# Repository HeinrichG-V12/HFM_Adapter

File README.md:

# HFM Adapter

## With this adapter it is possible to replace any HLM with any HFM

## Development status

- Hardware: Revision 1.0 done
  - [**Revision 1.0 is erroneous, swapped pins on TLE42764 and TLE4252D.**](./hardware/Rev1.0/README.md)
  - [Revision 1.1 done](./hardware/Rev1.1/README.md)
- Software: Version 1.0 done

### HFM Adapter based on

- STM32 G431KB Nucleo-32 Board
- ST M24M02 2MBit serial I²C EEPROM to store the tables and configuration
- TI REF02 +5.0v precision voltage reference, +-0.2%
- Infineon TLE4252D tracking regulator 250mA
- TI OPA2992 output operation amplifier

### Nucleo-32 modifications

A few changes need to be made to the Nucleo-32 board before it can be used:

- SB1 and SB12 removed (disconnect PA2 and PA3 from T_VCP_TX and T_VCP_RX of ST-Link)
- SB14 installed (connect PA3 to CN3 Pin 10)
- SB9 and SB10 installed (connect external 24MHz HSE CLK)

### Features

- Automotive grade components
- 4 layer PCB
- Configuration via TunerStudio

### Inputs

- two HFM buffered analog inputs (0v - 5v) with overvoltage protection 
- USB for configuration
- VBat input for voltage monitoring 

### Outputs

- two analog outputs
- two precision reference 5.0v outputs for HFM
- two Vbat outputs for HFM

### Housing

- Header: Amphenol ATM13-12PA
- Enclosure: Amphenol AIPXE-325X4

### Pin terminal for BMW M70 adapter

- pin terminal 1252 1718125
- connector boot 1252 1711262
- pins
  - 0.5 - 1.0mm² 6113 1376191
  - 1.0mm² - 2.5mm² 6113 1376193
  - 2.5mm² - 4.0mm² 6113 1376195

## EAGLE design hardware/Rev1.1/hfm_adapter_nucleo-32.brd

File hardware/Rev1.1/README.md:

# HFM Adapter

## Revision 1.1

[Schematic](./hfm_adapter_nucleo-32.pdf)

Pinout

|Pin#|Wire size|Main color|Second color|Signal|
|----|---------|----------|------------|------|
|1|0.5mm²|brown|-|signal ground|
|2|0.5mm²|brown|-|signal ground|
|3|0.5mm²|red|blue|VBat|
|4|0.5mm²|red|blue|VBat|
|5|0.5mm²|violett|black|5v reference voltage for HFM|
|6|0.5mm²|brown|-|signal ground|
|7|0.5mm²|red|blue|VBat|
|8|0.5mm²|violet|black|5v reference voltage for HFM|
|9|0.5mm²|violet|yellow|Channel 1 input from HFM|
|10|0.5mm²|orange|yellow|Channel 2 input from HFM|
|11|0.5mm²|violet|green|Channel 1 output to ECM|
|12|0.5mm²|orange|green|Channel 2 output to ECM|

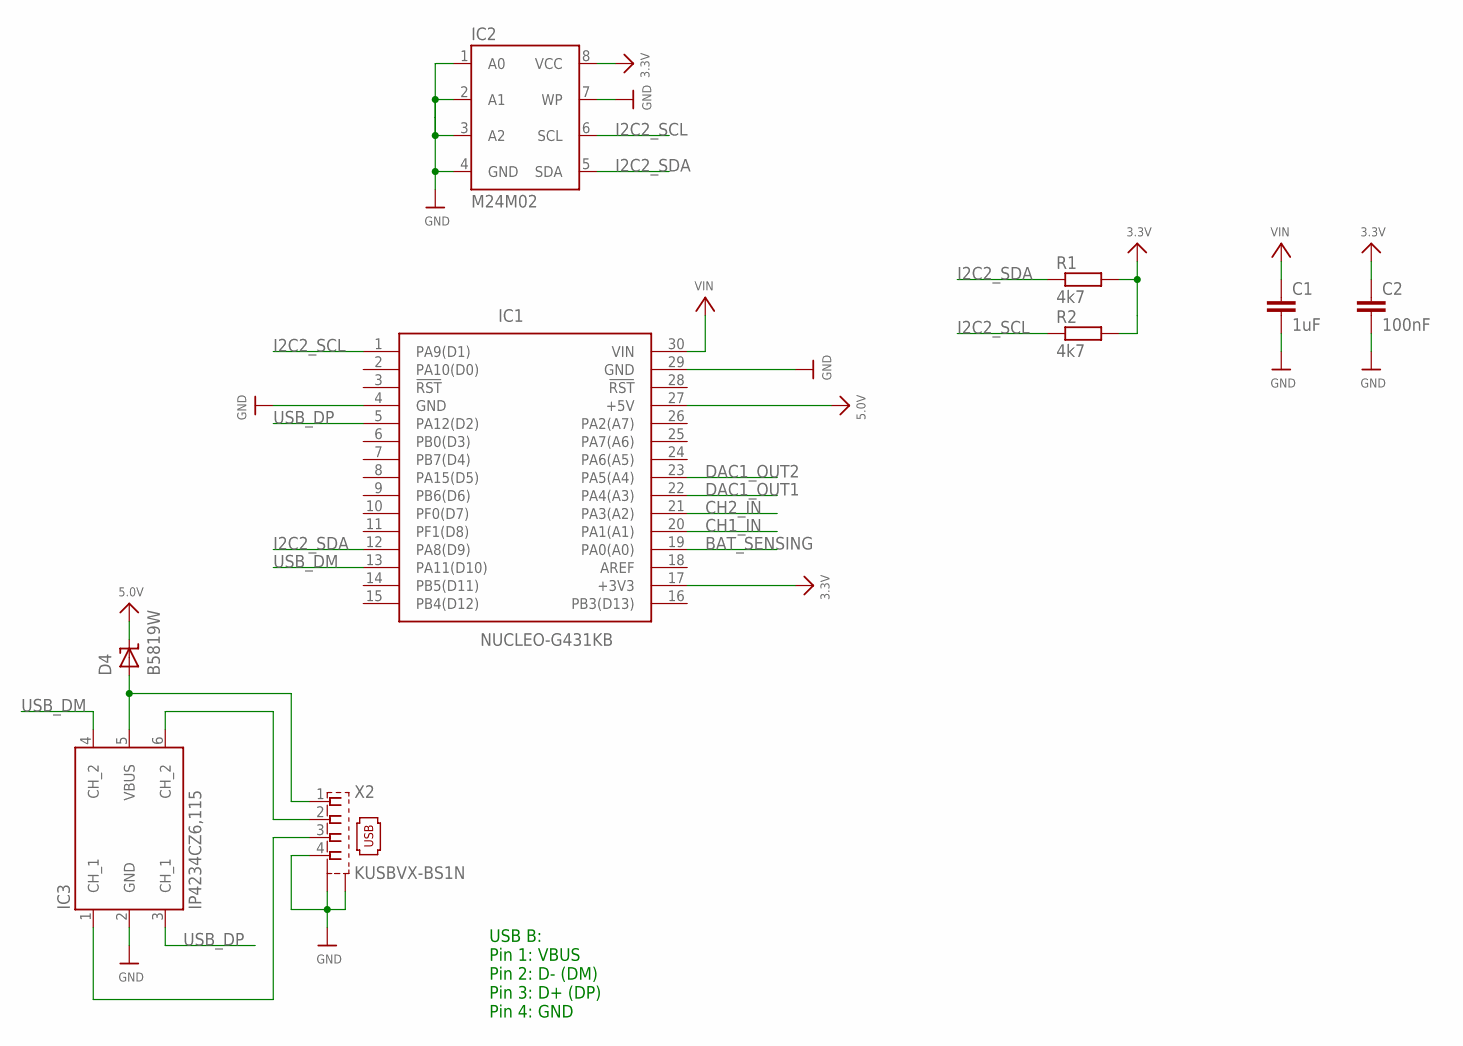
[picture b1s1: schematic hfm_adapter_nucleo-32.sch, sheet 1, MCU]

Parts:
C1: 1uF; C0805
C2: 100nF; C0805
D4: B5819W; SOD-123
IC1: NUCLEO-G431KB; DIPS1524W66P254L5029H1500Q30N
IC2: M24M02; SO8
IC3: IP4234CZ6,115; SOT95P275X110-6N
R1, R2: 4k7; R0805
X2: KUSBVX-BS1N

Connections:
3.3V: C2.1, IC1.17 (+3V3), IC2.8 (VCC), R1.2, R2.2; also elsewhere on the board
5.0V: D4.C, IC1.27 (+5V); also elsewhere on the board
BAT_SENSING: IC1.19 (PA0(A0)); also elsewhere on the board
CH1_IN: IC1.20 (PA1(A1)); also elsewhere on the board
CH2_IN: IC1.21 (PA3(A2)); also elsewhere on the board
DAC1_OUT1: IC1.22 (PA4(A3)); also elsewhere on the board
DAC1_OUT2: IC1.23 (PA5(A4)); also elsewhere on the board
GND: C1.2, C2.2, IC1.4 (GND), IC1.29 (GND), IC2.1 (A0), IC2.2 (A1), IC2.3 (A2), IC2.4 (GND), IC2.7 (WP), IC3.2 (GND), X2.4, X2.M1 (S1), X2.M2 (S2); also elsewhere on the board
I2C2_SCL: IC1.1 (PA9(D1)), IC2.6 (SCL), R2.1; also elsewhere on the board
I2C2_SDA: IC1.12 (PA8(D9)), IC2.5 (SDA), R1.1; also elsewhere on the board
unnamed: IC3.1 (CH_1), X2.3
unnamed: IC3.6 (CH_2), X2.2
unnamed: D4.A, IC3.5 (VBUS), X2.1
USB_DM: IC1.13 (PA11(D10)), IC3.4 (CH_2)
USB_DP: IC1.5 (PA12(D2)), IC3.3 (CH_1)
VIN: C1.1, IC1.30 (VIN); also elsewhere on the board

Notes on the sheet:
USB B: Pin 1: VBUS Pin 2: D- (DM) Pin 3: D+ (DP) Pin 4: GND

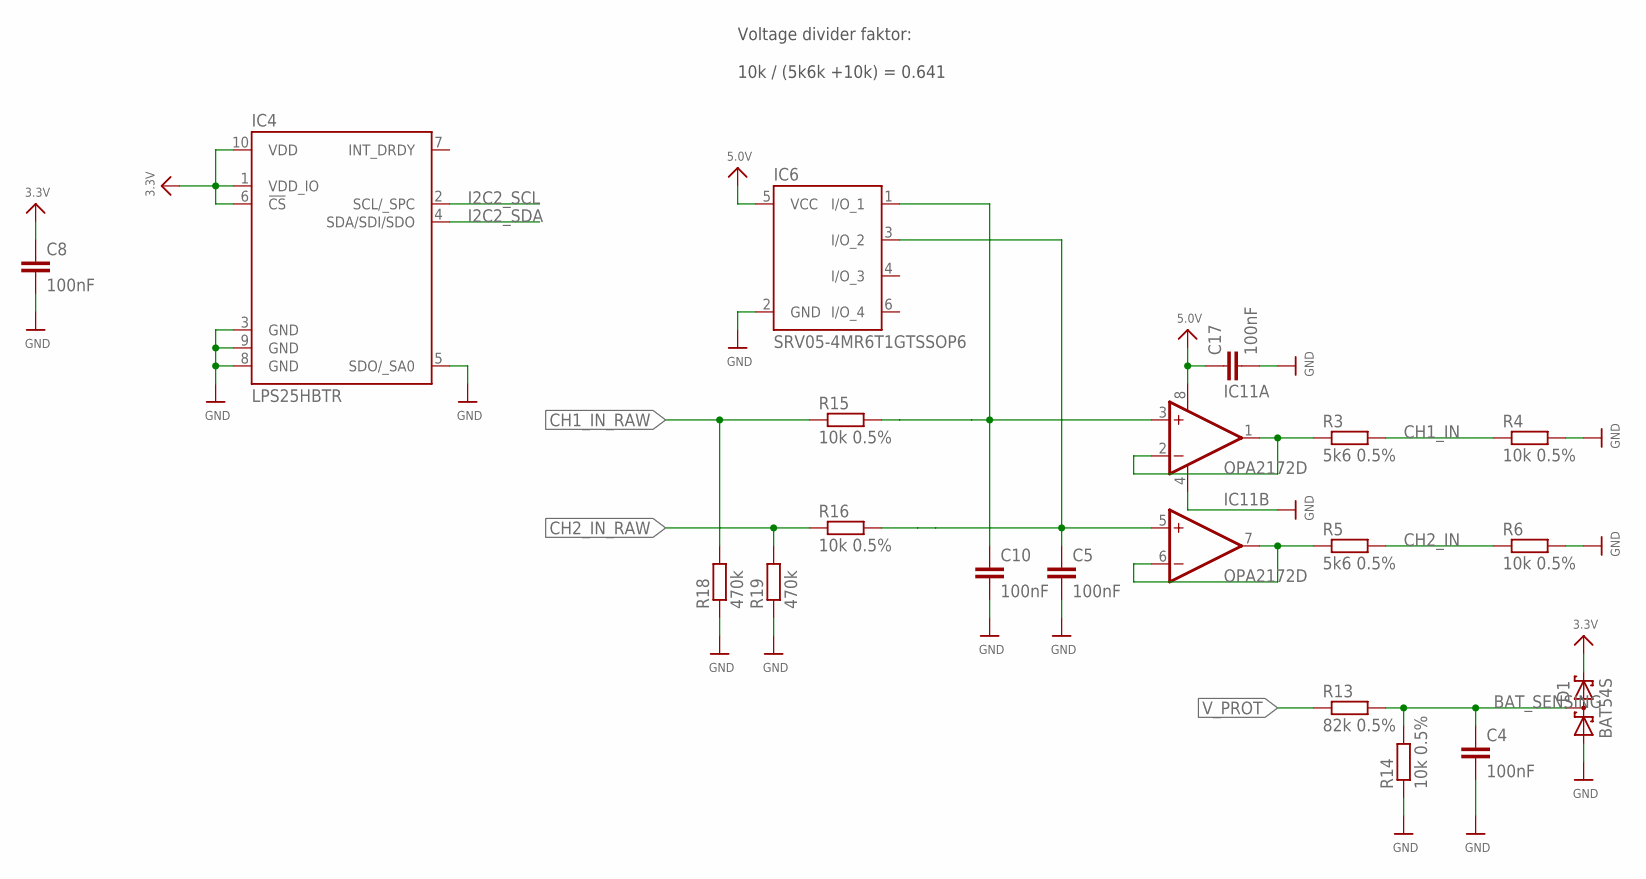
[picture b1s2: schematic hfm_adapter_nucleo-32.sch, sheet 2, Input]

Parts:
C4, C5, C8, C10, C17: 100nF; C0805
D1: BAT54S; SOT23
IC4: LPS25HBTR
IC6: SRV05-4MR6T1GTSSOP6; TSSOP6
IC11: OPA2172D; SO08
R3, R5: 5k6 0.5%; R0805
R4, R6, R14, R15, R16: 10k 0.5%; R0805
R13: 82k 0.5%; R0805
R18, R19: 470k; R0805

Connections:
3.3V: C8.1, D1.2 (K2), IC4.1 (VDD_IO), IC4.6 (!CS), IC4.10 (VDD); also elsewhere on the board
5.0V: C17.1, IC6.5 (VCC), IC11.8 (V+); also elsewhere on the board
BAT_SENSING: C4.1, D1.3 (K1A2), R13.2, R14.2; also elsewhere on the board
CH1_IN: R3.2, R4.1; also elsewhere on the board
CH1_IN_RAW: R15.1, R18.2; also elsewhere on the board
CH2_IN: R5.2, R6.1; also elsewhere on the board
CH2_IN_RAW: R16.1, R19.2; also elsewhere on the board
GND: C4.2, C5.2, C8.2, C10.2, C17.2, D1.1 (A1), IC4.3 (GND), IC4.5 (SDO/_SA0), IC4.8 (GND), IC4.9 (GND), IC6.2 (GND), IC11.4 (V-), R4.2, R6.2, R14.1, R18.1, R19.1; also elsewhere on the board
I2C2_SCL: IC4.2 (SCL/_SPC); also elsewhere on the board
I2C2_SDA: IC4.4 (SDA/SDI/SDO); also elsewhere on the board
unnamed: IC11.1 (OUT), IC11.2 (-IN), R3.1
unnamed: C10.1, IC6.1 (I/O_1), IC11.3 (+IN), R15.2
unnamed: IC11.6 (-IN), IC11.7 (OUT), R5.1
unnamed: C5.1, IC6.3 (I/O_2), IC11.5 (+IN), R16.2
V_PROT: R13.1; also elsewhere on the board

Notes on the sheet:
Voltage divider faktor: 10k / (5k6k +10k) = 0.641

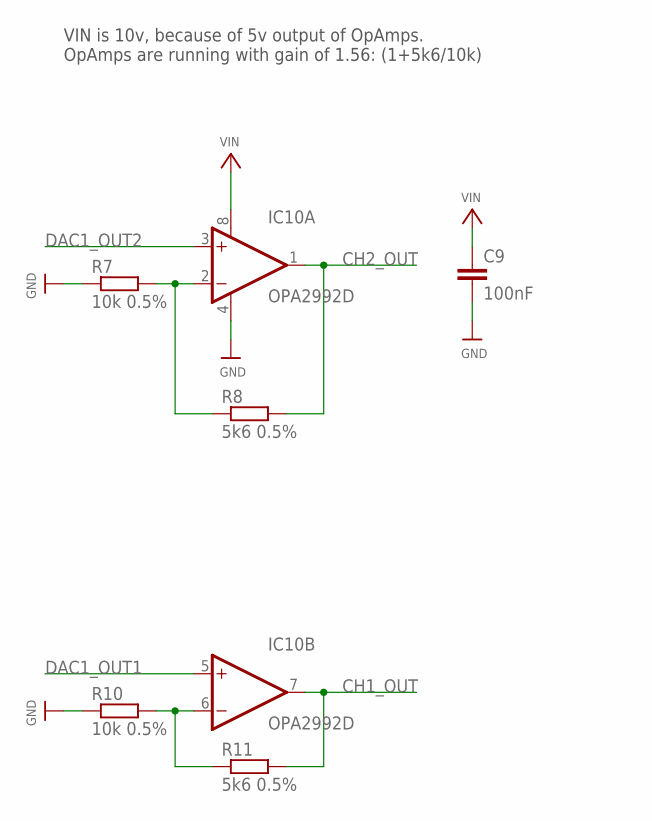
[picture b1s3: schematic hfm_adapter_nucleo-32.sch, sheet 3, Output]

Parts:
C9: 100nF; C0805
IC10: OPA2992D; SO08
R7, R10: 10k 0.5%; R0805
R8, R11: 5k6 0.5%; R0805

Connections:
CH1_OUT: IC10.7 (OUT), R11.2; also elsewhere on the board
CH2_OUT: IC10.1 (OUT), R8.2; also elsewhere on the board
DAC1_OUT1: IC10.5 (+IN); also elsewhere on the board
DAC1_OUT2: IC10.3 (+IN); also elsewhere on the board
GND: C9.2, IC10.4 (V-), R7.1, R10.1; also elsewhere on the board
unnamed: IC10.6 (-IN), R10.2, R11.1
unnamed: IC10.2 (-IN), R7.2, R8.1
VIN: C9.1, IC10.8 (V+); also elsewhere on the board

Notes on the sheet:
VIN is 10v, because of 5v output of OpAmps. OpAmps are running with gain of 1.56: (1+5k6/10k)

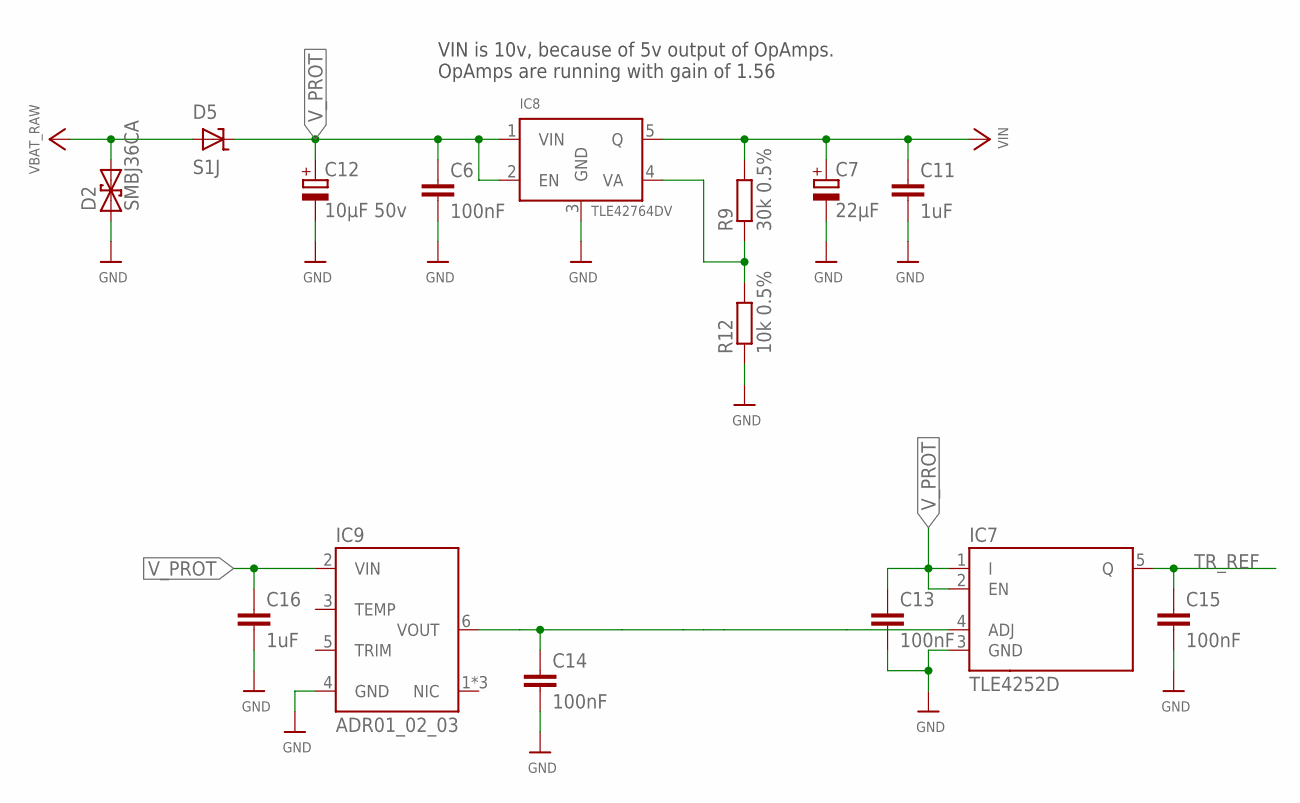
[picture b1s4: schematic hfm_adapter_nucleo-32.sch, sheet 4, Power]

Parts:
C6: 100nF; C1206
C7: 22µF; PANASONIC_C
C11, C16: 1uF; C0805
C12: 10µF 50v; PANASONIC_D
C13, C14, C15: 100nF; C0805
D2: SMBJ36CA; DO214AA
D5: S1J; DO214AC
IC7: TLE4252D; TO-252-5-INF
IC8: TLE42764DV; TO-252-5-INF
IC9: ADR01_02_03; SOIC8
R9: 30k 0.5%; R0805
R12: 10k 0.5%; R0805

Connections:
GND: C6.2, C7.-, C11.2, C12.-, C13.2, C14.2, C15.2, C16.2, D2.A (1), IC7.3 (GND), IC8.3 (GND), IC9.4 (GND), R12.1; also elsewhere on the board
unnamed: IC8.4 (VA), R9.1, R12.2
TR_REF: C15.1, IC7.5 (Q); also elsewhere on the board
VBAT_RAW: D2.C (2), D5.A; also elsewhere on the board
VIN: C7.+, C11.1, IC8.5 (Q), R9.2; also elsewhere on the board
VREF: C14.1, IC7.4 (ADJ), IC9.6 (VOUT)
V_PROT: C6.1, C12.+, C13.1, C16.1, D5.C, IC7.1 (I), IC7.2 (EN), IC8.1 (VIN), IC8.2 (EN), IC9.2 (VIN); also elsewhere on the board

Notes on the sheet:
VIN is 10v, because of 5v output of OpAmps. OpAmps are running with gain of 1.56

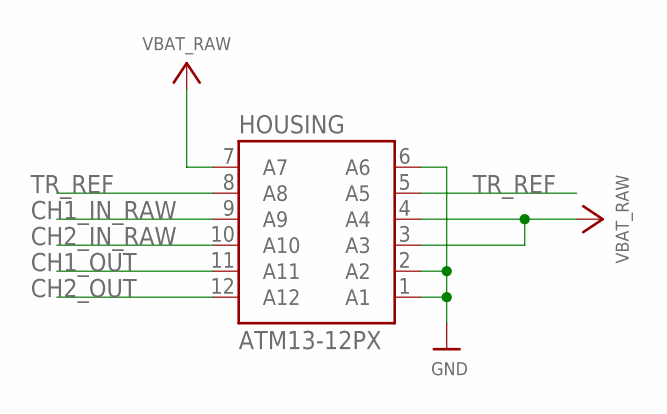
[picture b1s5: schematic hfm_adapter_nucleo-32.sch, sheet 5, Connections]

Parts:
HOUSING: ATM13-12PX

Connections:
CH1_IN_RAW: HOUSING.9 (A9); also elsewhere on the board
CH1_OUT: HOUSING.11 (A11); also elsewhere on the board
CH2_IN_RAW: HOUSING.10 (A10); also elsewhere on the board
CH2_OUT: HOUSING.12 (A12); also elsewhere on the board
GND: HOUSING.1 (A1), HOUSING.2 (A2), HOUSING.6 (A6); also elsewhere on the board
TR_REF: HOUSING.5 (A5), HOUSING.8 (A8); also elsewhere on the board
VBAT_RAW: HOUSING.3 (A3), HOUSING.4 (A4), HOUSING.7 (A7); also elsewhere on the board

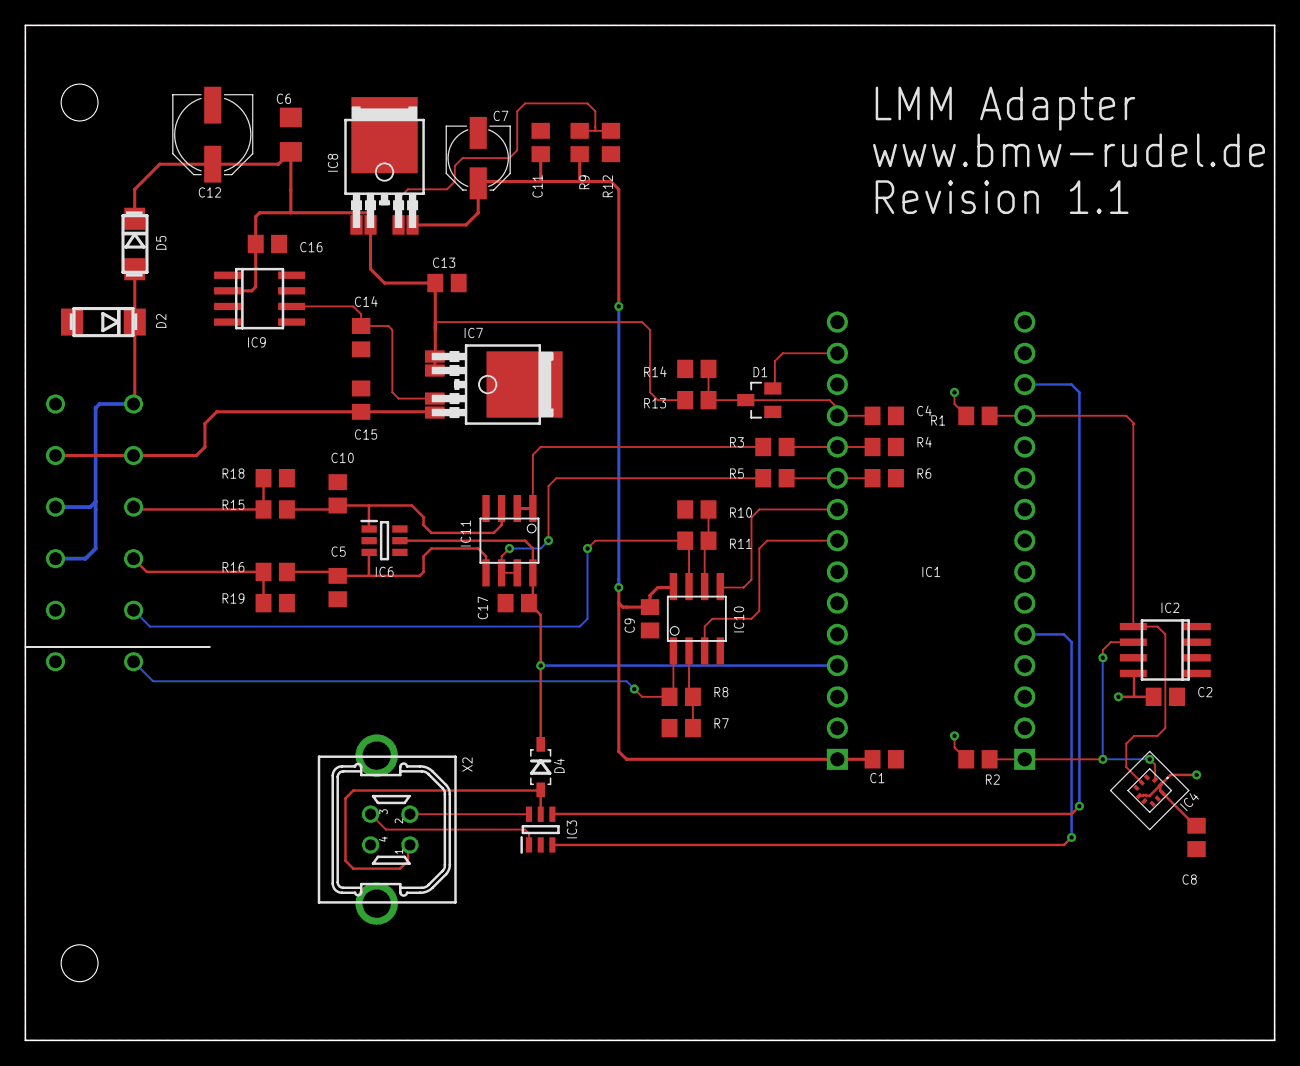
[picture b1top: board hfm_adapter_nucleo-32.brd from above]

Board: 4 copper layers, 101.6 x 82.5 mm, 50 parts (0 on the bottom side), 31 nets.

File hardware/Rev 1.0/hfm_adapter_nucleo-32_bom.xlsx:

Qty | Value | Device | Package | Parts | Description
10 | 100nF | C-EUC0805 | C0805 | C2, C4, C5, C8, C9, C10, C13, C14, C15, C17 | CAPACITOR, European symbol
1 | 100nF | C-EUC1206 | C1206 | C6 | CAPACITOR, European symbol
3 | 10k | R-EU_R0805 | R0805 | R14, R15, R16 | RESISTOR, European symbol
1 | 10k 0.5% | R-EU_R0805 | R0805 | R12 | RESISTOR, European symbol
1 | 10ÂµF 50v | CPOL-EUD | PANASONIC_D | C12 | POLARIZED CAPACITOR, European symbol
4 | 17k 0.5% | R-EU_R0805 | R0805 | R3, R5, R7, R10 | RESISTOR, European symbol
3 | 1uF | C-EUC0805 | C0805 | C1, C11, C16 | CAPACITOR, European symbol
1 | 22µF | CPOL-EUC | PANASONIC_C | C7 | POLARIZED CAPACITOR, European symbol
1 | 30k 0.5% | R-EU_R0805 | R0805 | R9 | RESISTOR, European symbol
4 | 33k 0.5% | R-EU_R0805 | R0805 | R4, R6, R8, R11 | RESISTOR, European symbol
2 | 470k | R-EU_R0805 | R0805 | R18, R19 | RESISTOR, European symbol
2 | 4k7 | R-EU_R0805 | R0805 | R1, R2 | RESISTOR, European symbol
1 | 82k | R-EU_R0805 | R0805 | R13 | RESISTOR, European symbol
1 | ATM13-12PX | ATM13-12PX | ATM13-12PX | HOUSING
1 | B5819W | SHOTTKYSOD-123 | SOD-123 | D4
1 | BAT54S | BAT54S | SOT23 | D1 | Schottky barrier (double) diodesPlanar Schottky barrier diodes encapsulated in 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
1 | IP4234CZ6,115 | IP4234CZ6,115 | SOT95P275X110-6N | IC3 | ESD Suppressors / TVS Diodes ESD PRTCT/HI SPD INF ZEN LOW VLTG CLMP
1 | KUSBVX-BS1N | KUSBVX-BS1N | KUSBVX-BS1N | X2 | USB B-type Receptacle Vertical, 4 Position, Through Hole
1 | LPS25HBTR | LPS25HBTR | LPS25HBTR | IC4 | Board Mount Pressure Sensor 26kPa to 126kPa Absolute 10-Pin HLGA T/R
1 | M24M02 | EEPROM_I2CSO8 | SO8 | IC2 | IÂ²C EEPROM IC, i.e. FT24C256A
1 | NUCLEO-G431KB | NUCLEO-G431KB | DIPS1524W66P254L5029H1500Q30N | IC1 | STM32 Nucleo-32 development board
1 | OPA2172D | OPA2172D | SO08 | IC11 | Operational Amplifier
1 | OPA2992D | OPA2172D | SO08 | IC10 | Operational Amplifier
1 | REF02D | REF02D | SO08 | IC5 | VOLTAGE REFERENCE
1 | S1J | SHOTTKYSMA | DO214AC | D5
1 | SMBJ36CA | TVS_BIA | DO214AA | D2
1 | SRV05-4MR6T1GTSSOP6 | SRV05-4MR6T1GTSSOP6 | TSSOP6 | IC6
1 | TLE4252D | TLE4252D | TO252-51 | IC9 | Infineon Tracking regualtor
1 | TLE42764_ADJDV | TLE42764_ADJDV | TO252-51 | IC8

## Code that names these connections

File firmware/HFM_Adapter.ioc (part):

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Mcu.Name=STM32G431K(6-8-B)Tx
Mcu.Package=LQFP32
Mcu.UserName=STM32G431KBTx
PA0.Mode=IN1-Single-Ended
PA0.Signal=ADC1_IN1
PA1.Mode=IN2-Single-Ended
PA1.Signal=ADC1_IN2
PA11.Mode=Device
PA11.Signal=USB_DM
PA12.Mode=Device
PA12.Signal=USB_DP
PA13.GPIOParameters=GPIO_Label
PA13.GPIO_Label=T_SWDIO
PA13.Mode=Serial_Wire
PA13.Signal=SYS_JTMS-SWDIO
PA14.GPIOParameters=GPIO_Label
PA14.GPIO_Label=T_SWCLK
PA14.Mode=Serial_Wire
PA14.Signal=SYS_JTCK-SWCLK
PA2.Mode=IN3-Single-Ended
PA2.Signal=ADC1_IN3
PA4.Signal=COMP_DAC11_group
PA5.Signal=COMP_DAC12_group
PA8.Mode=I2C
PA8.Signal=I2C2_SDA
PA9.Mode=I2C
PA9.Signal=I2C2_SCL
PB3.Signal=SYS_JTDO-SWO
PB4.GPIOParameters=GPIO_Label
PB4.GPIO_Label=USER
PB4.Signal=GPIO_Output
PB8-BOOT0.GPIOParameters=GPIO_Label
PB8-BOOT0.GPIO_Label=LD2
PB8-BOOT0.Signal=GPIO_Output
PF0-OSC_IN.Mode=HSE-External-Oscillator
PF0-OSC_IN.Signal=RCC_OSC_IN
PF1-OSC_OUT.Mode=HSE-External-Oscillator
PF1-OSC_OUT.Signal=RCC_OSC_OUT
RCC.HSE_VALUE=24000000
RCC.SYSCLKFreq_VALUE=144000000
RCC.SYSCLKSource=RCC_SYSCLKSOURCE_PLLCLK
board=NUCLEO-G431KB
boardIOC=true

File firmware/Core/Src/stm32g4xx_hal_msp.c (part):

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
    __HAL_RCC_GPIOA_CLK_ENABLE();
    /**ADC1 GPIO Configuration
    PA0     ------> ADC1_IN1
    PA1     ------> ADC1_IN2
    PA2     ------> ADC1_IN3
    */
    GPIO_InitStruct.Pin = GPIO_PIN_0|GPIO_PIN_1|GPIO_PIN_2;
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    __HAL_RCC_ADC12_CLK_DISABLE();

    /**ADC1 GPIO Configuration
    PA0     ------> ADC1_IN1
    PA1     ------> ADC1_IN2
    PA2     ------> ADC1_IN3
    */
    HAL_GPIO_DeInit(GPIOA, GPIO_PIN_0|GPIO_PIN_1|GPIO_PIN_2);
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
    __HAL_RCC_GPIOA_CLK_ENABLE();
    /**DAC1 GPIO Configuration
    PA4     ------> DAC1_OUT1
    PA5     ------> DAC1_OUT2
    */
    GPIO_InitStruct.Pin = GPIO_PIN_4|GPIO_PIN_5;
    GPIO_InitStruct.Mode = GPIO_MODE_ANALOG;
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    __HAL_RCC_DAC1_CLK_DISABLE();

    /**DAC1 GPIO Configuration
    PA4     ------> DAC1_OUT1
    PA5     ------> DAC1_OUT2
    */
    HAL_GPIO_DeInit(GPIOA, GPIO_PIN_4|GPIO_PIN_5);

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
    __HAL_RCC_GPIOA_CLK_ENABLE();
    /**I2C2 GPIO Configuration
    PA8     ------> I2C2_SDA
    PA9     ------> I2C2_SCL
    */
    GPIO_InitStruct.Pin = GPIO_PIN_8|GPIO_PIN_9;
    GPIO_InitStruct.Mode = GPIO_MODE_AF_OD;
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    __HAL_RCC_I2C2_CLK_DISABLE();

    /**I2C2 GPIO Configuration
    PA8     ------> I2C2_SDA
    PA9     ------> I2C2_SCL
    */
    HAL_GPIO_DeInit(GPIOA, GPIO_PIN_8);

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
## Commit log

2022-07-09 initial
2022-07-09 readme edited
2023-11-07 initial import
2023-11-07 firmware initial commit
2023-11-07 some small changes
2023-11-07 some changes
2023-11-09 usb stuff added
2023-11-30 running implementation
2023-12-16 adapter added
2024-05-24 Revision 1 done
2024-05-24 some infos for R1.0 corrected
2024-06-03 some values changed, BOM added
2024-07-19 some changed rev 1.0
2024-07-21 some changeds
2024-07-21 Revision 1.1
2024-07-25 wire stubs removed
2024-07-25 some minimal changes
2024-10-12 nucleo-32 modifications and correct schematic
2024-10-13 amplification factor corrected

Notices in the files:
firmware/Core/Src/stm32g4xx_hal_msp.c:
Copyright (c) 2023 STMicroelectronics.
All rights reserved.
This software is licensed under terms that can be found in the LICENSE file
parts and their libraries:
microbuilder: This work is placed in the public domain, and may be freely used for commercial and non-commercial work with the following conditions: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
